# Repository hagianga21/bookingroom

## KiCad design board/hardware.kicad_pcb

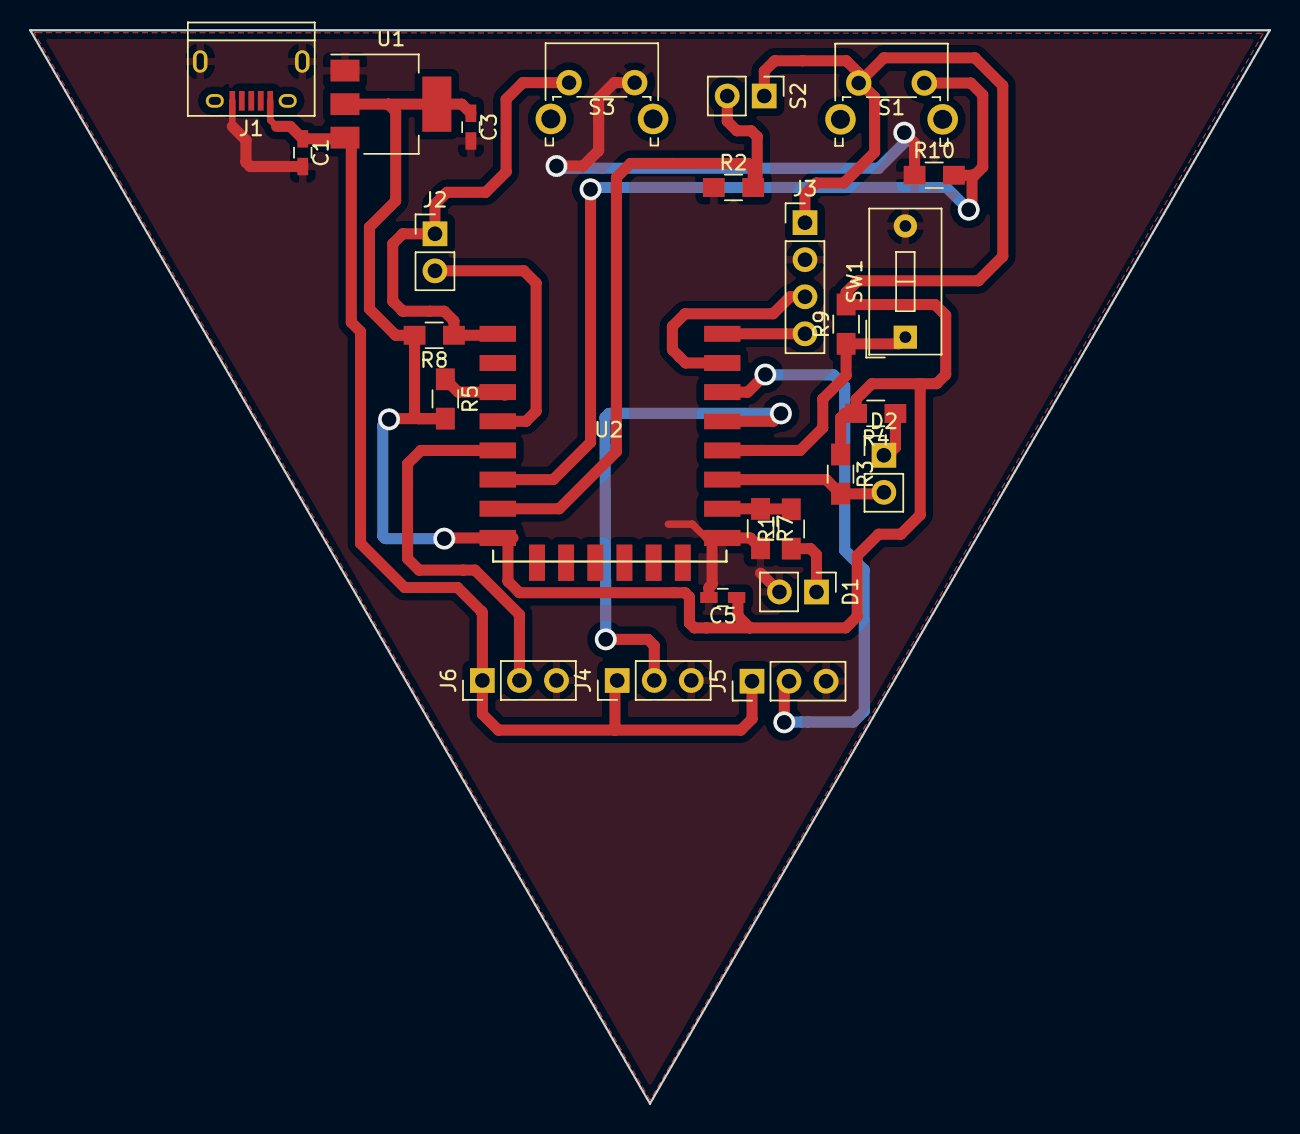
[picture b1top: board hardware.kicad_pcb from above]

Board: 2 copper layers, 85.0 x 73.6 mm, 26 parts (0 on the bottom side), 18 nets.

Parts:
C1, C3, C5: 104; C_0603_HandSoldering
D1: LED_SW; Pin_Header_Straight_1x02_Pitch2.54mm
D2: LED; Pin_Header_Straight_1x02_Pitch2.54mm
J1: USB_OTG; USB_Micro-B
J2: WAKE UP MODE; Pin_Header_Straight_1x02_Pitch2.54mm
J3: BUILD; Pin_Header_Straight_1x04_Pitch2.54mm
J4: SENSOR 1; Pin_Header_Straight_1x03_Pitch2.54mm
J5: SENSOR 2; Pin_Header_Straight_1x03_Pitch2.54mm
J6: SENSOR 3; Pin_Header_Straight_1x03_Pitch2.54mm
R1, R2, R4, R10: 1K; R_0805_HandSoldering
R3, R5, R7, R8, R9: 10K; R_0805_HandSoldering
S1: AP MODE; SW_Tactile_SPST_Angled_PTS645Vx83-2LFS
S2: BREAK; Pin_Header_Straight_1x02_Pitch2.54mm
S3: RESET; SW_Tactile_SPST_Angled_PTS645Vx83-2LFS
SW1: PROGRAM; SW_DIP_x1_W7.62mm_Slide
U1: AP1117; SOT-223
U2: ESP8266

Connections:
+3V3: C3.1, C5.1, J3.1, R3.1, R4.2, R5.2, R8.2, R9.2, S1.1, S2.1, U1.2, U1.4, U2.8
+5V: C1.1, J1.1, J4.1, J5.1, J6.1, U1.3
EN: R5.1, U2.3
GND: C1.2, C3.2, C5.2, D1.2, J1.5, J1.6, J3.2, J4.3, J5.3, J6.3, R2.1, R7.2, R10.1, S3.2, SW1.2, U1.1, U2.15
GPIO0: R9.1, SW1.1, U2.18
GPIO2: D2.2, R3.2, U2.17
GPIO4: J4.2, U2.19
GPIO5: J5.2, U2.20
GPIO12: R10.2, S1.2, U2.6
GPIO13: R2.2, S2.2, U2.7
GPIO14: J6.2, U2.5
GPIO15: R1.2, R7.1, U2.16
GPIO16: J2.2, U2.4
unnamed: D1.1, R1.1
unnamed: D2.1, R4.1
RST: J2.1, R8.1, S3.1, U2.1
RX: J3.4, U2.22
TX: J3.3, U2.21

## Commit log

2017-08-02 check
